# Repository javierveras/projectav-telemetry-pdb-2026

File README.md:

# Telemetry & Power Distribution System
Our power distribution and telemetry system's hardware, firmware, and technical documentation.

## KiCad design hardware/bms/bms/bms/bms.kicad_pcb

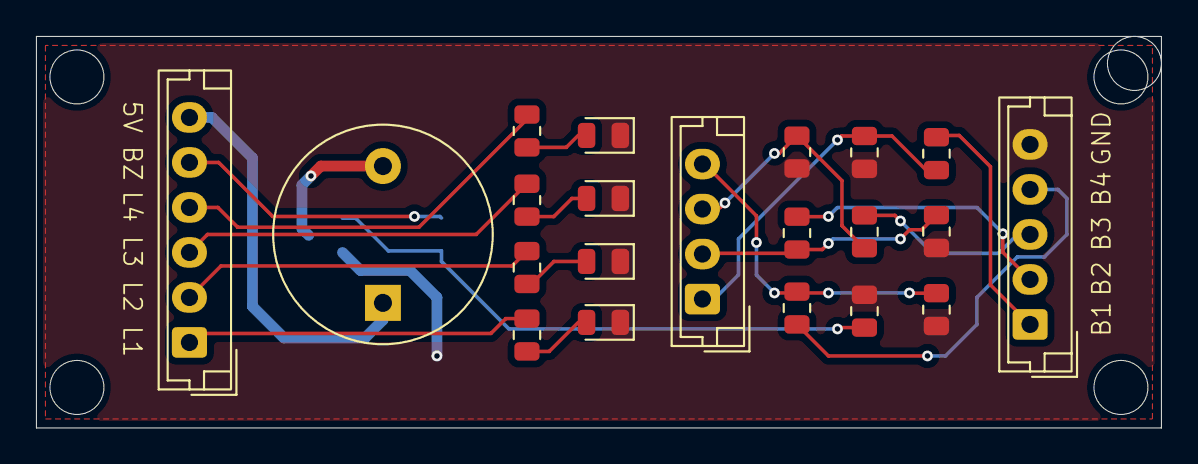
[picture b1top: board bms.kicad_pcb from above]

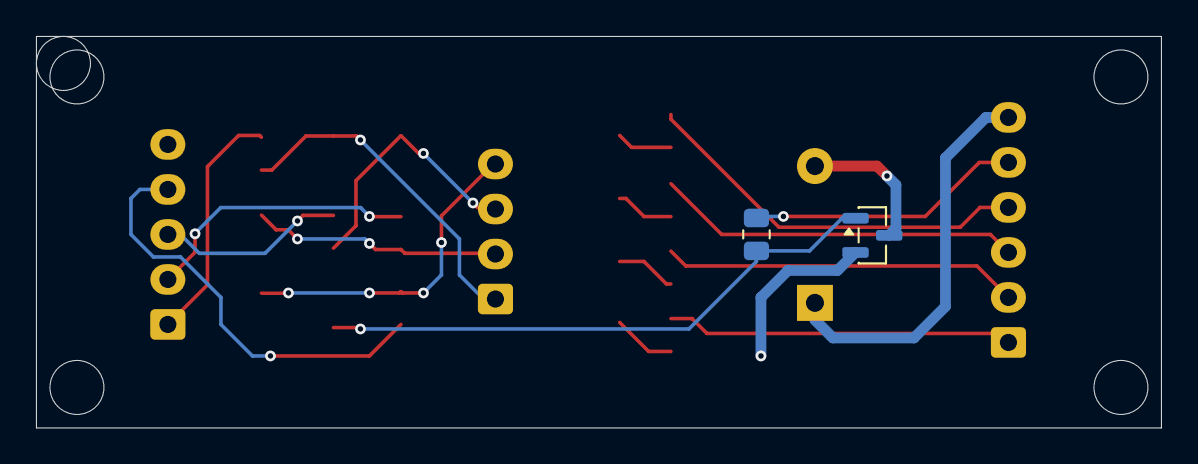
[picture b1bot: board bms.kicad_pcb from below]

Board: 2 copper layers, 62.5 x 21.8 mm, 23 parts (2 on the bottom side), 21 nets.

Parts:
BZ1: Buzzer; Buzzer_12x9.5RM7.6
D1, D2, D3, D4: LED; LED_0805_2012Metric
J1: OUTPUT; JST_EH_B4B-EH-A_1x04_P2.50mm_Vertical
J2: Conn_01x05_Pin; JST_EH_B5B-EH-A_1x05_P2.50mm_Vertical
J3: Conn_01x06_Pin; JST_EH_B6B-EH-A_1x06_P2.50mm_Vertical
Q1: Q_NPN_BEC; SOT-23
RBOTT5, RBOTT6, RBOTT7, RBOTT8: 10K; R_0805_2012Metric
RTOP5, RTOP6, RTOP7, RTOP8: 47K; R_0805_2012Metric
RTOP9, RTOP12, RTOP13, RTOP14: 680; R_0805_2012Metric
RTOP10: 1k; R_0805_2012Metric
RTOP11: 10k; R_0805_2012Metric

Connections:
/5V: BZ1.1 (+), J3.6
/BUZZER_GATE: J3.5, RTOP10.1
/LED1: J3.1, RTOP9.1
/LED2: J3.2, RTOP13.1
/LED3: J3.3, RTOP14.1
/LED4: J3.4, RTOP12.1
/MEASS_CELL1: J1.1, RBOTT5.1, RTOP5.2
/MEASS_CELL2: J1.2, RBOTT7.1, RTOP7.2
/MEASS_CELL3: J1.3, RBOTT6.1, RTOP6.2
/MEASS_CELL4: J1.4, RBOTT8.1, RTOP8.2
GND: D1.1 (K), D2.1 (K), D3.1 (K), D4.1 (K), J2.5, Q1.2 (E), RBOTT5.2, RBOTT6.2, RBOTT7.2, RBOTT8.2, RTOP11.1
unnamed: BZ1.2 (-), Q1.3 (C)
unnamed: D1.2 (A), RTOP9.2
unnamed: D2.2 (A), RTOP12.2
unnamed: D3.2 (A), RTOP13.2
unnamed: D4.2 (A), RTOP14.2
unnamed: Q1.1 (B), RTOP10.2, RTOP11.2
RAW_CELL1: J2.1, RTOP5.1
RAW_CELL2: J2.2, RTOP7.1
RAW_CELL3: J2.3, RTOP6.1
RAW_CELL4: J2.4, RTOP8.1

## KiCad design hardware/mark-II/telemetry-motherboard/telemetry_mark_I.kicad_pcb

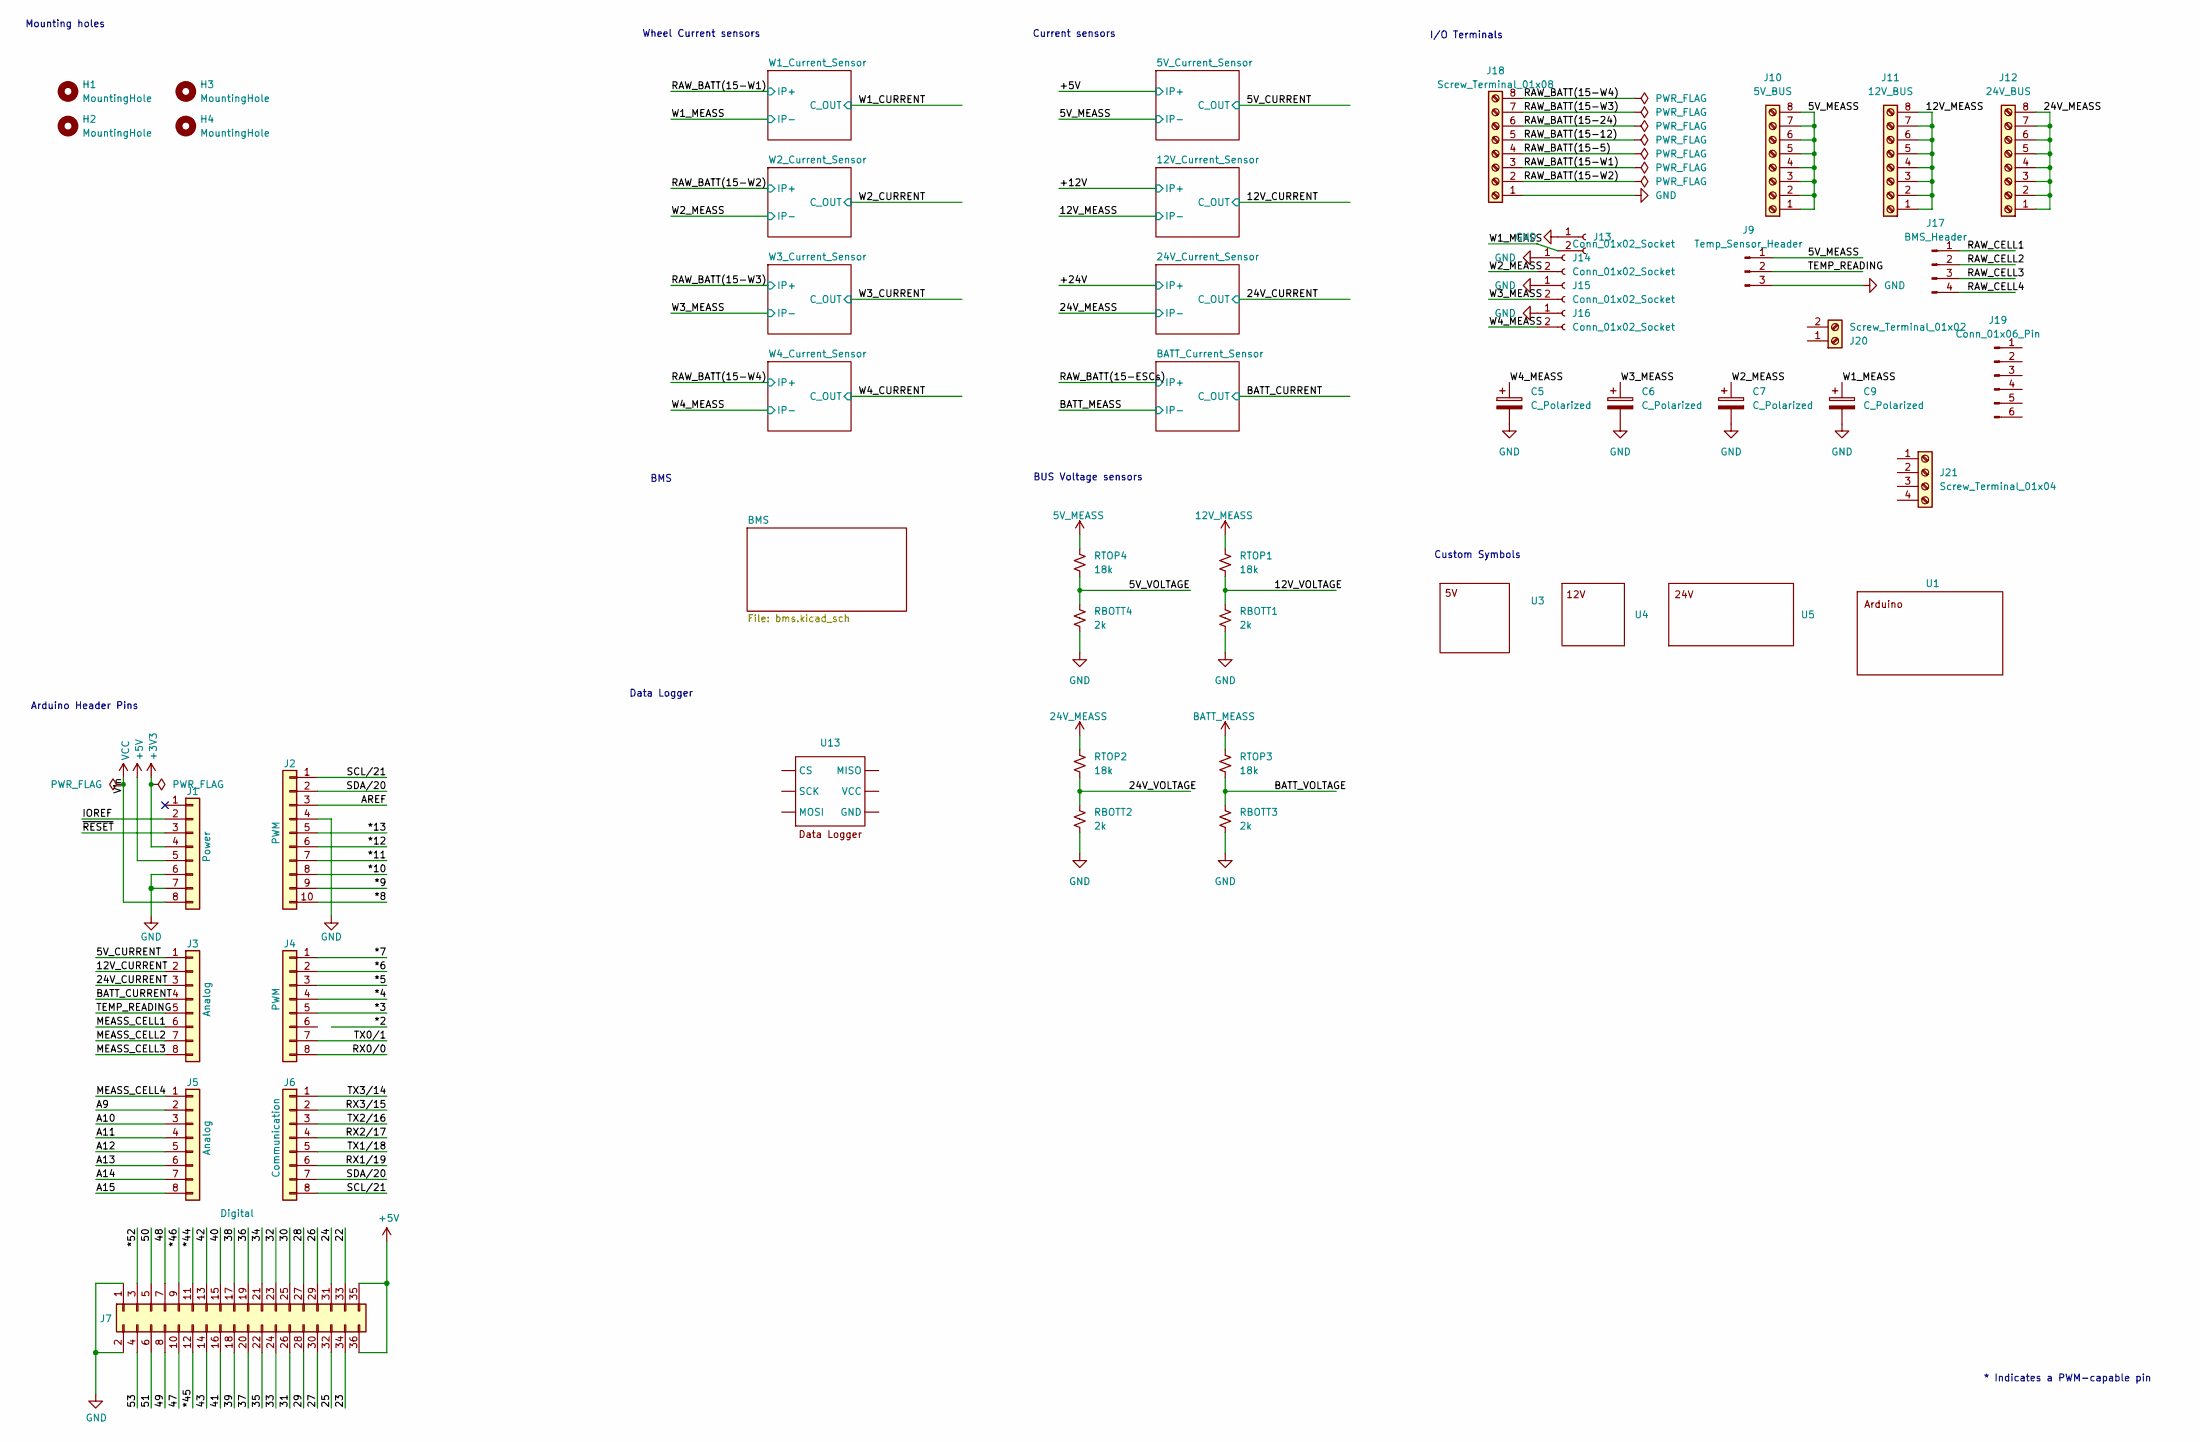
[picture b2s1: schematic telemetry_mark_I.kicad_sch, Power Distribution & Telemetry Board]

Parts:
C5, C6, C7, C9: C_Polarized; CP_Elec_8x10.5
H1, H2, H3, H4: MountingHole; MountingHole_4mm_Pad
J1: Power; PinHeader_1x08_P2.54mm_Vertical
J2: PWM; PinHeader_1x10_P2.54mm_Vertical
J3, J5: Analog; PinHeader_1x08_P2.54mm_Vertical
J4: PWM; PinHeader_1x08_P2.54mm_Vertical
J6: Communication; PinHeader_1x08_P2.54mm_Vertical
J7: Digital; PinHeader_2x18_P2.54mm_Vertical
J9: Temp_Sensor_Header; JST_EH_B3B-EH-A_1x03_P2.50mm_Vertical
J10: 5V_BUS; TerminalBlock_Phoenix_MKDS-1,5-8-5.08_1x08_P5.08mm_Horizont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
J11: 12V_BUS; TerminalBlock_Phoenix_MKDS-1,5-8_1x08_P5.00mm_Horizontal
J12: 24V_BUS; TerminalBlock_Phoenix_MKDS-1,5-8_1x08_P5.00mm_Horizontal
J13, J14, J15, J16: Conn_01x02_Socket; AMASS_XT60PW-F_1x02_P7.20mm_Horizontal
J17: BMS_Header; JST_XH_B5B-XH-A_1x05_P2.50mm_Vertical
J18: Screw_Terminal_01x08; TerminalBlock_Ningbo-Kagnex_HB9500_1x08_P9.5mm
J19: Conn_01x06_Pin; PinSocket_1x06_P2.54mm_Horizontal
J20: Screw_Terminal_01x02; TerminalBlock_Phoenix_MKDS-1,5-2-5.08_1x02_P5.08mm_Horizont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
J21: Screw_Terminal_01x04; PhoenixContact_MCV_1,5_4-GF-3.81_1x04_P3.81mm_Vertical_Thre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
RBOTT1, RBOTT2, RBOTT3, RBOTT4: 2k; R_0603_1608Metric_Pad0.98x0.95mm_HandSolder
RTOP1, RTOP2, RTOP3, RTOP4: 18k; R_0603_1608Metric_Pad0.98x0.95mm_HandSolder
U1: ArduinoMega
U3: Untitled
U4: Untitled_1
U5: 24Converter
U13: Untitled_3

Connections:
5V_MEASS: J9.1, J10.1, J10.2, J10.3, J10.4, J10.5, J10.6, J10.7, J10.8, RTOP4.1; also elsewhere on the board
12V_MEASS: RTOP1.1; also elsewhere on the board
24V_MEASS: RTOP2.1; also elsewhere on the board
+3V3: J1.4
+5V: J1.5, J7.35, J7.36; also elsewhere on the board
/5V_CURRENT: J3.1; also elsewhere on the board
/5V_VOLTAGE: RBOTT4.1, RTOP4.2
/12V_CURRENT: J3.2; also elsewhere on the board
/12V_VOLTAGE: RBOTT1.1, RTOP1.2
/22: J7.33
/23: J7.34
/24: J7.31
/24V_CURRENT: J3.3; also elsewhere on the board
/24V_VOLTAGE: RBOTT2.1, RTOP2.2
/25: J7.32
/26: J7.29
/27: J7.30
/28: J7.27
/29: J7.28
/30: J7.25
/31: J7.26
/32: J7.23
/33: J7.24
/34: J7.21
/35: J7.22
/36: J7.19
/37: J7.20
/38: J7.17
/39: J7.18
/40: J7.15
/41: J7.16
/42: J7.13
/43: J7.14
/47: J7.10
/48: J7.7
/49: J7.8
/50: J7.5
/51: J7.6
/53: J7.4
/*3: J4.5
/*4: J4.4
/*5: J4.3
/*6: J4.2
/*7: J4.1
/*8: J2.10
/*9: J2.9
/*10: J2.8
/*11: J2.7
/*12: J2.6
/*13: J2.5
/*44: J7.11
/*45: J7.12
/*46: J7.9
/*52: J7.3
/A9: J5.2
/A10: J5.3
/A11: J5.4
/A12: J5.5
/A13: J5.6
/A14: J5.7
/A15: J5.8
/AREF: J2.3
/BATT_CURRENT: J3.4; also elsewhere on the board
/BATT_VOLTAGE: RBOTT3.1, RTOP3.2
/IOREF: J1.2
/MEASS_CELL1: J3.6
/MEASS_CELL2: J3.7
/MEASS_CELL3: J3.8
/MEASS_CELL4: J5.1
/RAW_BATT(15-5): J18.4
/RAW_BATT(15-12): J18.5
/RAW_BATT(15-24): J18.6
/RAW_BATT(15-W1): J18.3; also elsewhere on the board
/RAW_BATT(15-W2): J18.2; also elsewhere on the board
/RAW_BATT(15-W3): J18.7; also elsewhere on the board
/RAW_BATT(15-W4): J18.8; also elsewhere on the board
/RAW_CELL1: J17.1
/RAW_CELL2: J17.2
/RAW_CELL3: J17.3
/RAW_CELL4: J17.4
/RX0/0: J4.8
/RX1/19: J6.6
/RX2/17: J6.4
/RX3/15: J6.2
/SCL/21: J2.1, J6.8
/SDA/20: J2.2, J6.7
/TEMP_READING: J3.5, J9.2
/TX0/1: J4.7
/TX1/18: J6.5
/TX2/16: J6.3
/TX3/14: J6.1
/W1_MEASS: C9.1, J13.2; also elsewhere on the board
/W2_MEASS: C7.1, J14.2; also elsewhere on the board
/W3_MEASS: C6.1, J15.2; also elsewhere on the board
/W4_MEASS: C5.1, J16.2; also elsewhere on the board
/~RESET: J1.3
BATT_MEASS: RTOP3.1; also elsewhere on the board
GND: C5.2, C6.2, C7.2, C9.2, J1.6, J1.7, J2.4, J7.1, J7.2, J9.3, J13.1, J14.1, J15.1, J16.1, J18.1, RBOTT1.2, RBOTT2.2, RBOTT3.2, RBOTT4.2; also elsewhere on the board
unnamed: J11.1, J11.2, J11.3, J11.4, J11.5, J11.6, J11.7, J11.8
unnamed: J12.1, J12.2, J12.3, J12.4, J12.5, J12.6, J12.7, J12.8
VCC: J1.8

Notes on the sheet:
BMS
Arduino Header Pins
I/O Terminals
Data Logger
Current sensors
Mounting holes
Wheel Current sensors
BUS Voltage sensors
* Indicates a PWM-capable pin
Custom Symbols

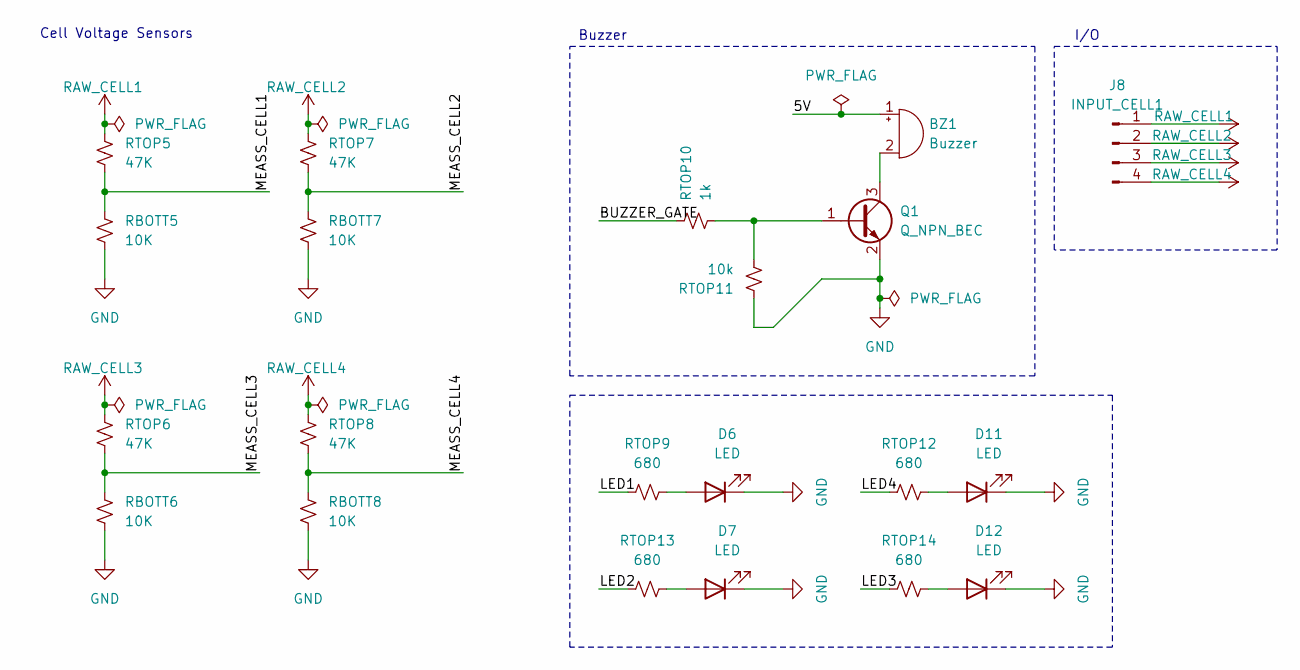
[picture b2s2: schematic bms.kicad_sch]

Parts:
BZ1: Buzzer; Buzzer_12x9.5RM7.6
D6, D7, D11, D12: LED; LED_1206_3216Metric
J8: INPUT_CELL1; PinHeader_1x04_P2.54mm_Vertical
Q1: Q_NPN_BEC; SOT-23
RBOTT5, RBOTT6, RBOTT7, RBOTT8: 10K; R_0805_2012Metric
RTOP5, RTOP6, RTOP7, RTOP8: 47K; R_0805_2012Metric
RTOP9, RTOP12, RTOP13, RTOP14: 680; R_0805_2012Metric
RTOP10: 1k; R_0805_2012Metric
RTOP11: 10k; R_0805_2012Metric

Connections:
/BMS/5V: BZ1.1 (+)
/BMS/BUZZER_GATE: RTOP10.1
/BMS/LED1: RTOP9.1
/BMS/LED2: RTOP13.1
/BMS/LED3: RTOP14.1
/BMS/LED4: RTOP12.1
/BMS/MEASS_CELL1: RBOTT5.1, RTOP5.2
/BMS/MEASS_CELL2: RBOTT7.1, RTOP7.2
/BMS/MEASS_CELL3: RBOTT6.1, RTOP6.2
/BMS/MEASS_CELL4: RBOTT8.1, RTOP8.2
GND: D6.1 (K), D7.1 (K), D11.1 (K), D12.1 (K), Q1.2 (E), RBOTT5.2, RBOTT6.2, RBOTT7.2, RBOTT8.2, RTOP11.1; also elsewhere on the board
unnamed: BZ1.2 (-), Q1.3 (C)
unnamed: D6.2 (A), RTOP9.2
unnamed: D7.2 (A), RTOP13.2
unnamed: D11.2 (A), RTOP12.2
unnamed: D12.2 (A), RTOP14.2
unnamed: Q1.1 (B), RTOP10.2, RTOP11.2
RAW_CELL1: J8.1, RTOP5.1
RAW_CELL2: J8.2, RTOP7.1
RAW_CELL3: J8.3, RTOP6.1
RAW_CELL4: J8.4, RTOP8.1

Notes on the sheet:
I/O
Buzzer
Cell Voltage Sensors

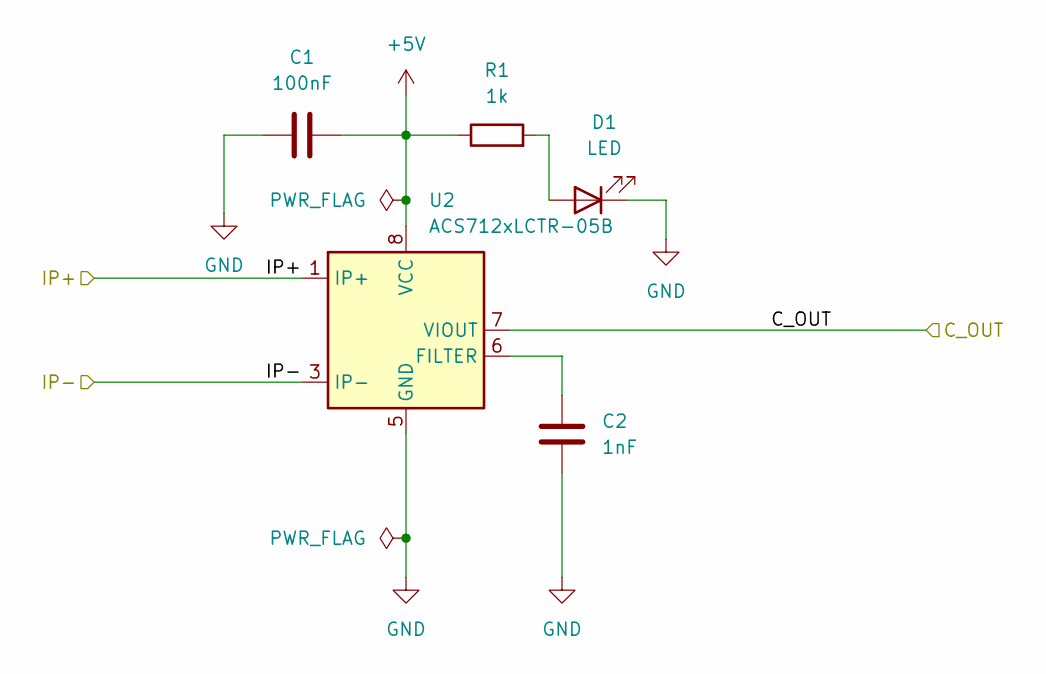
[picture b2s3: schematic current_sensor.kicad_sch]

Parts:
C1: 100nF; C_0805_2012Metric
C2: 1nF; C_0805_2012Metric
D1: LED; LED_0805_2012Metric
R1: 1k; R_0805_2012Metric
U2: ACS712xLCTR-05B; SOIC-8_3.9x4.9mm_P1.27mm

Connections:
5V_MEASS: U2.3 (IP-), U2.4 (IP-); also elsewhere on the board
+5V: C1.2, R1.1, U2.1 (IP+), U2.2 (IP+), U2.8 (VCC); also elsewhere on the board
/5V_CURRENT: U2.7 (VIOUT); also elsewhere on the board
GND: C1.1, C2.2, D1.1 (K), U2.5 (GND); also elsewhere on the board
unnamed: D1.2 (A), R1.2
unnamed: C2.1, U2.6 (FILTER)

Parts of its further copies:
C3, C8, C13, C16, C26, C30, C32: 100nF; C_0805_2012Metric
C4, C10, C15, C21, C29, C31, C33: 1nF; C_0805_2012Metric
D2, D3, D4, D5, D8, D9, D10: LED; LED_0805_2012Metric
R4, R5, R6, R7, R9, R10, R11: 1k; R_0805_2012Metric
U6, U7, U8, U9, U10, U11, U12: ACS712xLCTR-05B; SOIC-8_3.9x4.9mm_P1.27mm

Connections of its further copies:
12V_MEASS: U6.3 (IP-), U6.4 (IP-); also elsewhere on the board
24V_MEASS: U7.3 (IP-), U7.4 (IP-); also elsewhere on the board
+5V: C3.2, C8.2, C13.2, C16.2, C26.2, C30.2, C32.2, R4.1, R5.1, R6.1, R7.1, R9.1, R10.1, R11.1, U6.8 (VCC), U7.8 (VCC), U8.8 (VCC), U9.8 (VCC), U10.8 (VCC), U11.8 (VCC), U12.8 (VCC); also elsewhere on the board
/12V_CURRENT: U6.7 (VIOUT); also elsewhere on the board
/24V_CURRENT: U7.7 (VIOUT); also elsewhere on the board
/+12V: U6.1 (IP+), U6.2 (IP+)
/+24V: U7.1 (IP+), U7.2 (IP+)
/BATT_CURRENT: U8.7 (VIOUT); also elsewhere on the board
/RAW_BATT(15-ESCs): U8.1 (IP+), U8.2 (IP+)
/RAW_BATT(15-W1): U9.1 (IP+), U9.2 (IP+); also elsewhere on the board
/RAW_BATT(15-W2): U10.1 (IP+), U10.2 (IP+); also elsewhere on the board
/RAW_BATT(15-W3): U11.1 (IP+), U11.2 (IP+); also elsewhere on the board
/RAW_BATT(15-W4): U12.1 (IP+), U12.2 (IP+); also elsewhere on the board
/W1_CURRENT: U9.7 (VIOUT)
/W1_MEASS: U9.3 (IP-), U9.4 (IP-); also elsewhere on the board
/W2_CURRENT: U10.7 (VIOUT)
/W2_MEASS: U10.3 (IP-), U10.4 (IP-); also elsewhere on the board
/W3_CURRENT: U11.7 (VIOUT)
/W3_MEASS: U11.3 (IP-), U11.4 (IP-); also elsewhere on the board
/W4_CURRENT: U12.7 (VIOUT)
/W4_MEASS: U12.3 (IP-), U12.4 (IP-); also elsewhere on the board
BATT_MEASS: U8.3 (IP-), U8.4 (IP-); also elsewhere on the board
GND: C3.1, C4.2, C8.1, C10.2, C13.1, C15.2, C16.1, C21.2, C26.1, C29.2, C30.1, C31.2, C32.1, C33.2, D2.1 (K), D3.1 (K), D4.1 (K), D5.1 (K), D8.1 (K), D9.1 (K), D10.1 (K), U6.5 (GND), U7.5 (GND), U8.5 (GND), U9.5 (GND), U10.5 (GND), U11.5 (GND), U12.5 (GND); also elsewhere on the board
unnamed: D2.2 (A), R4.2
unnamed: D3.2 (A), R5.2
unnamed: D4.2 (A), R6.2
unnamed: D5.2 (A), R7.2
unnamed: D8.2 (A), R9.2
unnamed: D9.2 (A), R10.2
unnamed: D10.2 (A), R11.2
unnamed: C4.1, U6.6 (FILTER)
unnamed: C10.1, U7.6 (FILTER)
unnamed: C15.1, U8.6 (FILTER)
unnamed: C21.1, U9.6 (FILTER)
unnamed: C29.1, U10.6 (FILTER)
unnamed: C31.1, U11.6 (FILTER)
unnamed: C33.1, U12.6 (FILTER)

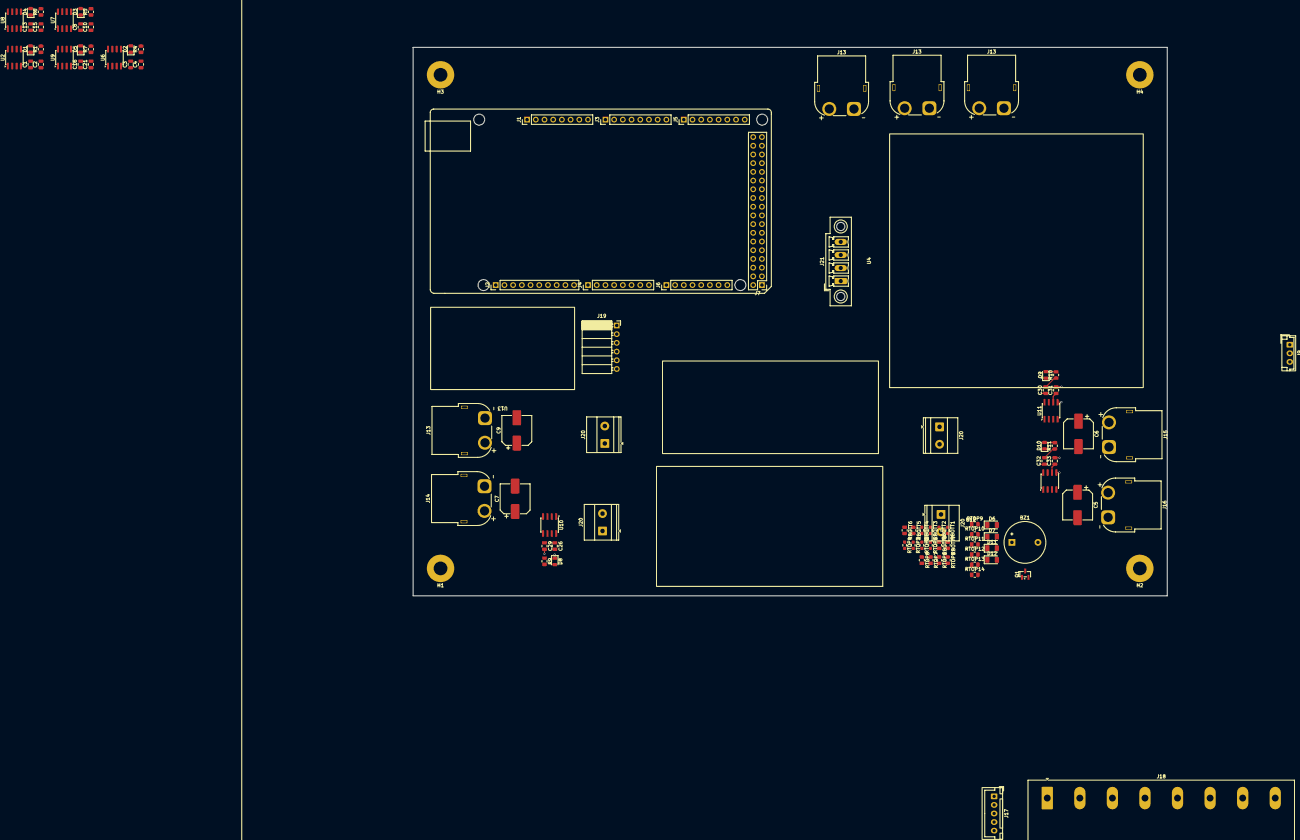
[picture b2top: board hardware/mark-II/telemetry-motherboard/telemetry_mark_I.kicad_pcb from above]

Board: 4 copper layers, 220.0 x 160.0 mm, 108 parts (0 on the bottom side), 54 nets.

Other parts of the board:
J13#2, J13#3, J13#4: Conn_01x02_Socket; AMASS_XT60PW-F_1x02_P7.20mm_Horizontal
J20#2, J20#3, J20#4: Screw_Terminal_01x02; TerminalBlock_Phoenix_MKDS-1,5-2-5.08_1x02_P5.08mm_Horizont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
MH1, MH2, MH5, MH6: MountingHole_3.2mm

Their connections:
/W1_MEASS: J13#4.2; also elsewhere on the board
GND: J13#4.1; also elsewhere on the board

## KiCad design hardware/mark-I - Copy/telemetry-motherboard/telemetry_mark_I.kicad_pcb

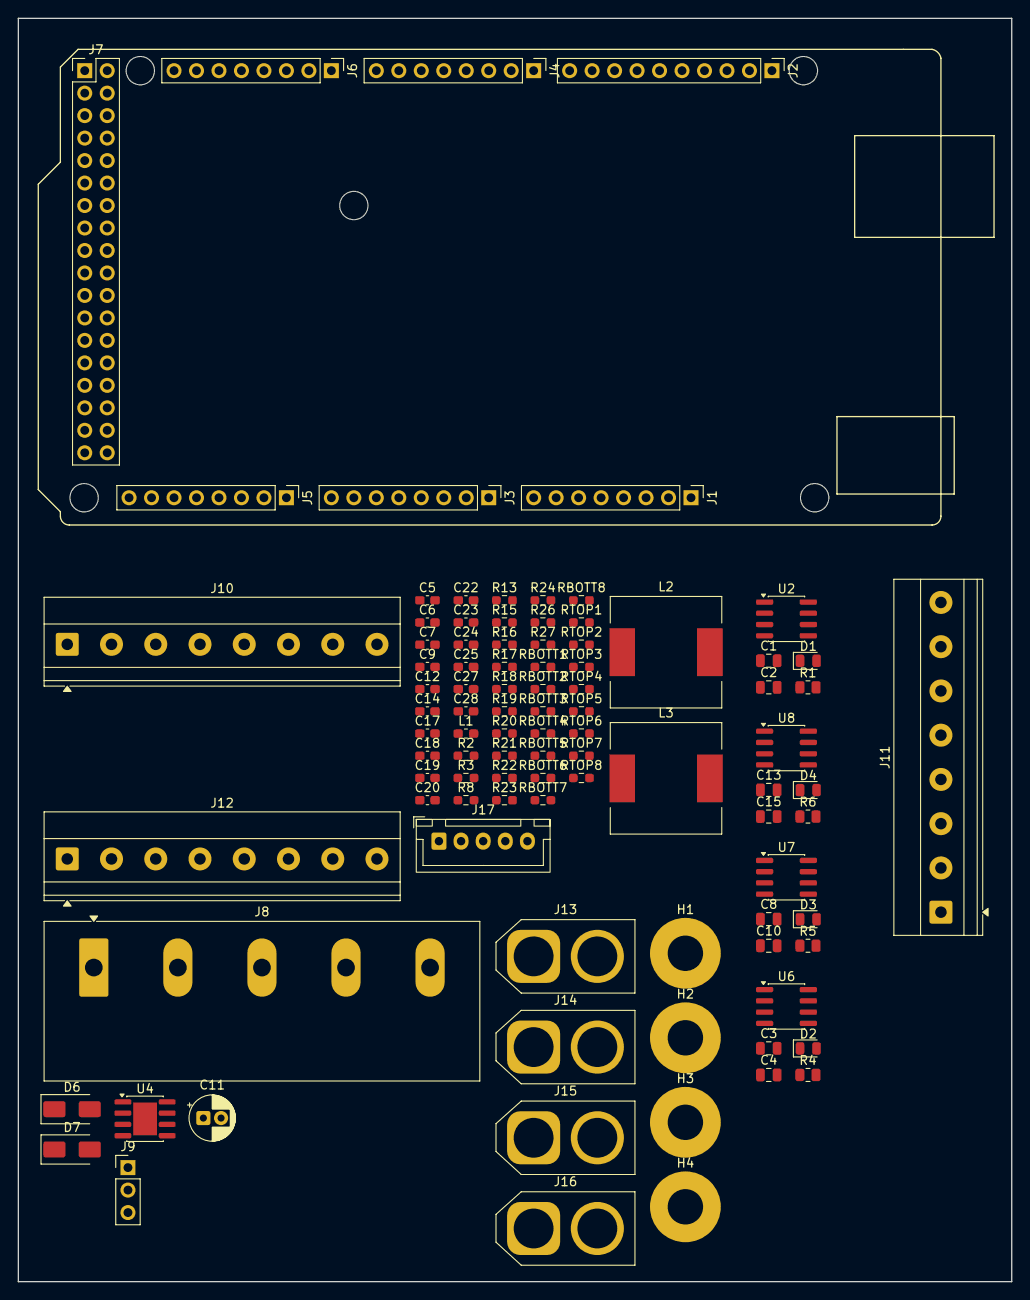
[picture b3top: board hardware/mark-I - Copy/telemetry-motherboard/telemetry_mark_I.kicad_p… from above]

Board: 2 copper layers, 112.2 x 142.8 mm, 101 parts (0 on the bottom side), 56 nets, no tracks yet.

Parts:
C1, C3, C8, C13: 100nF; C_0805_2012Metric
C2, C4, C10, C15: 1nF; C_0805_2012Metric
C5, C6: 68n; C_0603_1608Metric_Pad1.08x0.95mm_HandSolder
C7: 33n; C_0603_1608Metric_Pad1.08x0.95mm_HandSolder
C9: 4.7u; C_0603_1608Metric_Pad1.08x0.95mm_HandSolder
C11: 30u; CP_Radial_D5.0mm_P2.00mm
C12, C17, C19, C27, C28: 10u; C_0603_1608Metric_Pad1.08x0.95mm_HandSolder
C14: 4.7n; C_0603_1608Metric_Pad1.08x0.95mm_HandSolder
C18, C20: 0.3n; C_0603_1608Metric_Pad1.08x0.95mm_HandSolder
C22, C23: 1n; C_0603_1608Metric_Pad1.08x0.95mm_HandSolder
C24, C25: 100n; C_0603_1608Metric_Pad1.08x0.95mm_HandSolder
D1, D2, D3, D4: LED; LED_0805_2012Metric
D6, D7: SS54; D_SMA
H1, H2, H3, H4: MountingHole; MountingHole_4mm_Pad
J1: Power; PinHeader_1x08_P2.54mm_Vertical
J2: PWM; PinHeader_1x10_P2.54mm_Vertical
J3, J5: Analog; PinHeader_1x08_P2.54mm_Vertical
J4: PWM; PinHeader_1x08_P2.54mm_Vertical
J6: Communication; PinHeader_1x08_P2.54mm_Vertical
J7: Digital; PinHeader_2x18_P2.54mm_Vertical
J8: Input_Terminal; TerminalBlock_Ningbo-Kagnex_HB9500_1x05_P9.5mm
J9: Temp_Sensor_Header; PinHeader_1x03_P2.54mm_Vertical
J10: 5V_BUS; TerminalBlock_Phoenix_MKDS-1,5-8_1x08_P5.00mm_Horizontal
J11: 12V_BUS; TerminalBlock_Phoenix_MKDS-1,5-8_1x08_P5.00mm_Horizontal
J12: 24V_BUS; TerminalBlock_Phoenix_MKDS-1,5-8_1x08_P5.00mm_Horizontal
J13, J14, J15, J16: Conn_01x02_Socket; AMASS_XT60-F_1x02_P7.20mm_Vertical
J17: BMS_Header; JST_XH_B5B-XH-A_1x05_P2.50mm_Vertical
L1: 6.8u; L_0603_1608Metric_Pad1.05x0.95mm_HandSolder
L2, L3: 22u; L_12x12mm_H8mm
MH1, MH2, MH3, MH5, MH6: MountingHole_3.2mm
R1, R4, R5, R6: 1k; R_0805_2012Metric
R2: 20k; R_0603_1608Metric_Pad0.98x0.95mm_HandSolder
R3: 120k; R_0603_1608Metric_Pad0.98x0.95mm_HandSolder
R8: 2.8M; R_0603_1608Metric_Pad0.98x0.95mm_HandSolder
R13: 27.4k; R_0603_1608Metric_Pad0.98x0.95mm_HandSolder
R15: 43.2k; R_0603_1608Metric_Pad0.98x0.95mm_HandSolder
R16, R26: 105k; R_0603_1608Metric_Pad0.98x0.95mm_HandSolder
R17, R18: 47k; R_0603_1608Metric_Pad0.98x0.95mm_HandSolder
R19, R21: 680k; R_0603_1608Metric_Pad0.98x0.95mm_HandSolder
R20, R22: 100k; R_0603_1608Metric_Pad0.98x0.95mm_HandSolder
R23: 52.3k; R_0603_1608Metric_Pad0.98x0.95mm_HandSolder
R24: 10k; R_0603_1608Metric_Pad0.98x0.95mm_HandSolder
R27: 7.5k; R_0603_1608Metric_Pad0.98x0.95mm_HandSolder
RBOTT1, RBOTT2, RBOTT3, RBOTT4: 2k; R_0603_1608Metric_Pad0.98x0.95mm_HandSolder
RBOTT5, RBOTT6, RBOTT7, RBOTT8: 10K; R_0603_1608Metric_Pad0.98x0.95mm_HandSolder
RTOP1, RTOP2, RTOP3, RTOP4: 18k; R_0603_1608Metric_Pad0.98x0.95mm_HandSolder
RTOP5, RTOP6, RTOP7, RTOP8: 47K; R_0603_1608Metric_Pad0.98x0.95mm_HandSolder
U2, U6, U7, U8: ACS712xLCTR-05B; SOIC-8_3.9x4.9mm_P1.27mm
U4: AOZ1284PI; SOIC-8-1EP_3.9x4.9mm_P1.27mm_EP2.71x3.7mm

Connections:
5V_MEASS: J9.1, J10.1, J10.2, J10.3, J10.4, J10.5, J10.6, J10.7, J10.8, RTOP4.1, U2.3 (IP-), U2.4 (IP-)
12V_MEASS: J11.1, J11.2, J11.3, J11.4, J11.5, J11.6, J11.7, J11.8, RTOP1.1, U6.3 (IP-), U6.4 (IP-)
24V_MEASS: J12.1, J12.2, J12.3, J12.4, J12.5, J12.6, J12.7, J12.8, RTOP2.1, U7.3 (IP-), U7.4 (IP-)
+5V: C1.2, C3.2, C8.2, C13.2, C27.1, J1.5, J7.35, J7.36, L2.2, R1.1, R4.1, R5.1, R6.1, R23.1, U2.1 (IP+), U2.2 (IP+), U2.8 (VCC), U6.8 (VCC), U7.8 (VCC), U8.8 (VCC)
+12V: C28.1, L3.2, R26.1, U6.1 (IP+), U6.2 (IP+)
+24V: C11.1, R8.2, U7.1 (IP+), U7.2 (IP+)
/5V_CURRENT: J3.1, U2.7 (VIOUT)
/5V_VOLTAGE: RBOTT4.1, RTOP4.2
/12V_CURRENT: J3.2, U6.7 (VIOUT)
/12V_VOLTAGE: RBOTT1.1, RTOP1.2
/24V_CURRENT: J3.3, U7.7 (VIOUT)
/24V_VOLTAGE: RBOTT2.1, RTOP2.2
/BATT_CURRENT: J3.4, U8.7 (VIOUT)
/BATT_VOLTAGE: RBOTT3.1, RTOP3.2
/MEASS_CELL1: J3.6, RBOTT5.1, RTOP5.2
/MEASS_CELL2: J3.7, RBOTT7.1, RTOP7.2
/MEASS_CELL3: J3.8, RBOTT6.1, RTOP6.2
/MEASS_CELL4: J5.1, RBOTT8.1, RTOP8.2
/RAW_BATT(15-5): C17.1, J8.1, R19.1, U4.9 (VIN)
/RAW_BATT(15-12): C19.1, J8.2, R21.1
/RAW_BATT(15-24): C12.1, J8.3
/RAW_BATT(15-ESCs): J8.4, U8.1 (IP+), U8.2 (IP+)
/SCL/21: J2.1, J6.8
/SDA/20: J2.2, J6.7
/TEMP_READING: J3.5, J9.2
BATT_MEASS: J13.1, J14.1, J15.1, J16.1, RTOP3.1, U8.3 (IP-), U8.4 (IP-)
GND: C1.1, C2.2, C3.1, C4.2, C7.2, C8.1, C9.2, C10.2, C11.2, C12.2, C13.1, C15.2, C17.2, C19.2, C22.2, C23.2, C27.2, C28.2, D1.1 (K), D2.1 (K), D3.1 (K), D4.1 (K), D6.2 (A), D7.2 (A), J1.6, J1.7, J2.4, J7.1, J7.2, J9.3, J13.2, J14.2, J15.2, J16.2, R2.2, R3.1, R13.2, R15.2, R16.2, R17.2, R18.2, R20.2, R22.2, R24.2, R27.2, RBOTT1.2, RBOTT2.2, RBOTT3.2, RBOTT4.2, RBOTT5.2, RBOTT6.2, RBOTT7.2, RBOTT8.2, U2.5 (GND), U4.3 (GND), U6.5 (GND), U7.5 (GND), U8.5 (GND)
unnamed: C14.2, R13.1
unnamed: C18.1, R15.1
unnamed: C20.1, R16.1
unnamed: D1.2 (A), R1.2
unnamed: D2.2 (A), R4.2
unnamed: D3.2 (A), R5.2
unnamed: D4.2 (A), R6.2
unnamed: C24.2, D6.1 (K), L2.1, U4.1 (LX)
unnamed: C25.2, D7.1 (K), L3.1
unnamed: C2.1, U2.6 (FILTER)
unnamed: R3.2, R8.1
unnamed: C7.1, R2.1
unnamed: C6.1, L1.2
unnamed: C5.1, L1.1
unnamed: C24.1, U4.2 (BST)
unnamed: C18.2, U4.5 (COMP)
unnamed: R19.2, R20.1, U4.8 (EN)
unnamed: R23.2, R24.1, U4.6 (FB)
unnamed: R17.1, U4.4 (FSW)
unnamed: C22.1, U4.7 (SS)
unnamed: R21.2, R22.1
unnamed: R26.2, R27.1
unnamed: C4.1, U6.6 (FILTER)
unnamed: C10.1, U7.6 (FILTER)
unnamed: C15.1, U8.6 (FILTER)
RAW_CELL1: J17.1, RTOP5.1
RAW_CELL2: J17.2, RTOP7.1
RAW_CELL3: J17.3, RTOP6.1
RAW_CELL4: J17.4, RTOP8.1
